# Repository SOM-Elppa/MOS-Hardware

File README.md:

# MOS-Hardware
Modules for the MOS

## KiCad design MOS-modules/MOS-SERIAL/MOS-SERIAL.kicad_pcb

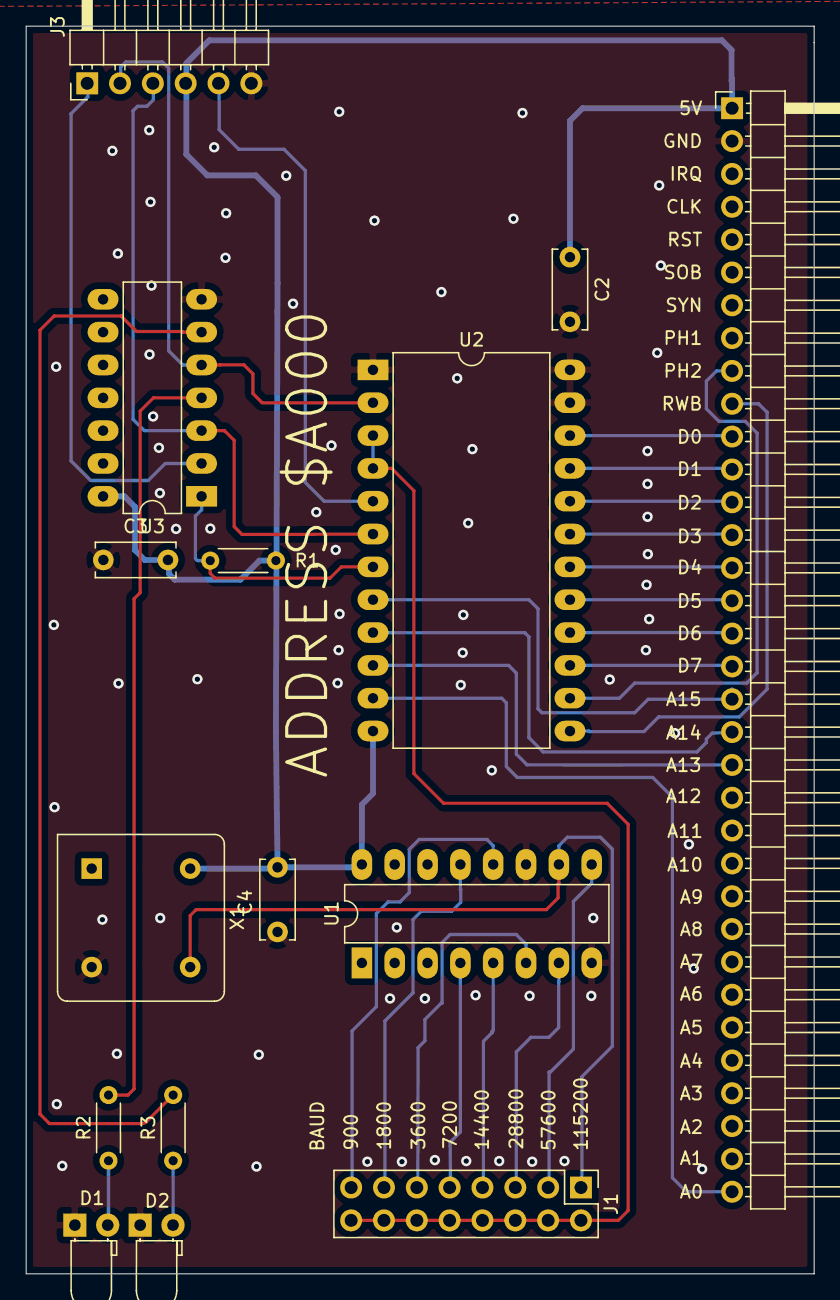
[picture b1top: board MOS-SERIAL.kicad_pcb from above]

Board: 2 copper layers, 61.0 x 96.5 mm, 15 parts (0 on the bottom side), 34 nets.

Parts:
C2: 100µF; C_Disc_D6.0mm_W2.5mm_P5.00mm
C3, C4: 100nF; C_Disc_D6.0mm_W2.5mm_P5.00mm
D1: LED TX; LED_D3.0mm_Horizontal_O1.27mm_Z2.0mm
D2: LED RX; LED_D3.0mm_Horizontal_O1.27mm_Z2.0mm
J1: Conn_02x08_Odd_Even; PinHeader_2x08_P2.54mm_Vertical
J2: Conn_01x34_Male; PinHeader_1x34_P2.54mm_Horizontal
J3: FTDI; PinHeader_1x06_P2.54mm_Horizontal
R1: 2k2; R_Axial_DIN0204_L3.6mm_D1.6mm_P5.08mm_Horizontal
R2, R3: 330R; R_Axial_DIN0204_L3.6mm_D1.6mm_P5.08mm_Horizontal
U1: 4020; DIP-16_W7.62mm_LongPads
U2: MC68B50; DIP-24_W15.24mm_LongPads
U3: 74LS04; DIP-14_W7.62mm_LongPads
X1: CXO_DIP8; Oscillator_DIP-8

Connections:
+5V: C2.1, C3.1, C4.1, J2.1, J3.4, R1.2, U1.16, U2.12, U3.14, X1.8
/900: J1.15, U1.12
/1800: J1.13, U1.13
/3600: J1.11, U1.6
/7200: J1.9, U1.4
/14400: J1.7, U1.5
/28800: J1.5, U1.7
/57600: J1.3, U1.9
/115200: J1.1, U1.10, X1.5
/A0: J2.34, U2.11
/A13: J2.21, U2.10
/A14: J2.20, U2.9
/A15: J2.19, U2.8
/CLK_SERIAL: J1.2, J1.4, J1.6, J1.8, J1.10, J1.12, J1.14, J1.16, U2.3, U2.4
/CTS: J3.5, U2.5
/D0: J2.11, U2.22
/D1: J2.12, U2.21
/D2: J2.13, U2.20
/D3: J2.14, U2.19
/D4: J2.15, U2.18
/D5: J2.16, U2.17
/D6: J2.17, U2.16
/D7: J2.18, U2.15
/DTR: J3.1, U3.2
/PHI2: J2.9, U2.14
/RWB: J2.10, U2.13
/RX: J3.2, U2.2, U3.5
/RXLED: D2.2, R3.1
/TX: J3.3, U2.6, U3.3
/TXLED: D1.2, R2.1
GND: C2.2, C3.2, C4.2, D1.1, D2.1, J2.2, J3.6, U1.8, U1.11, U2.1, U2.23, U2.24, U3.7, X1.4
unnamed: R1.1, U2.7, U3.1
unnamed: R2.2, U3.4
unnamed: R3.2, U3.6

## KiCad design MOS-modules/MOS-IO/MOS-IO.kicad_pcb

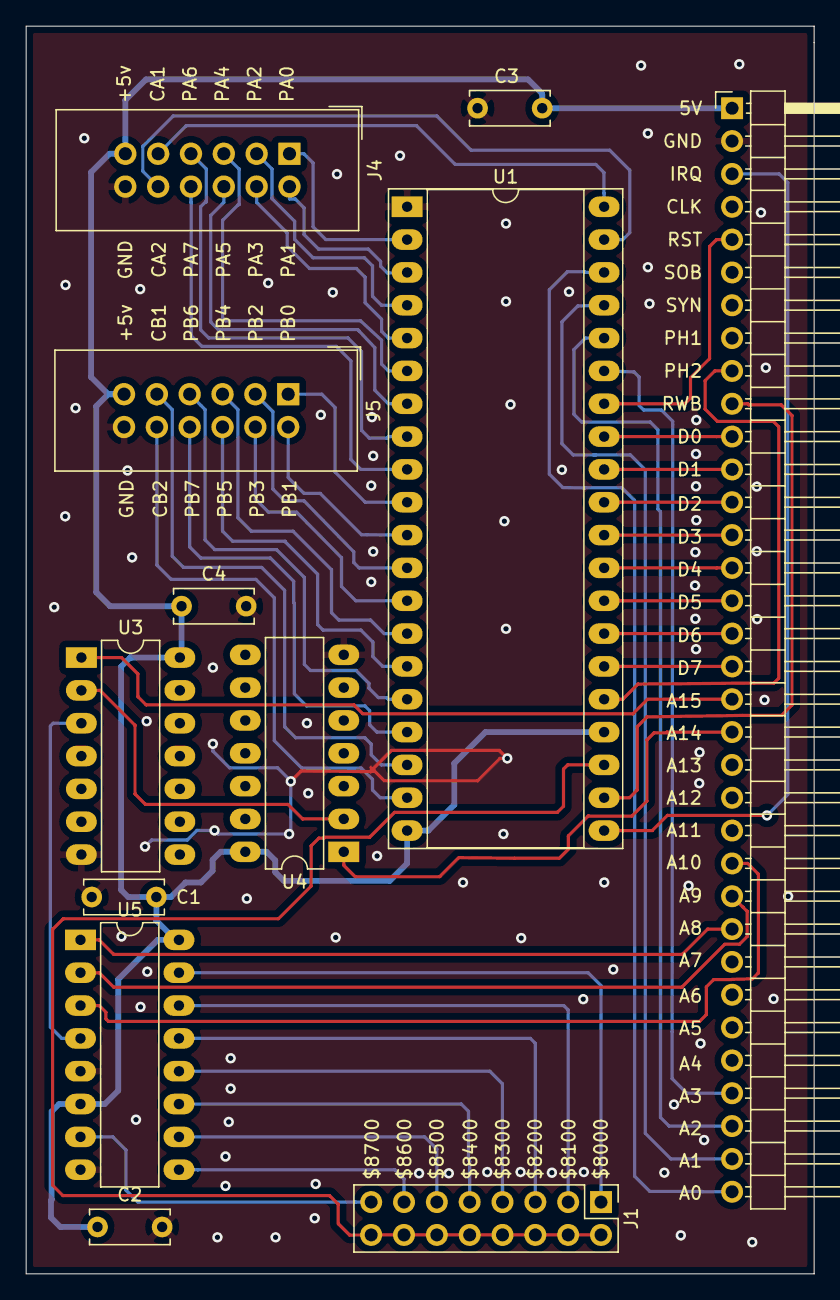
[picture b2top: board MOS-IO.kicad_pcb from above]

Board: 2 copper layers, 61.0 x 96.5 mm, 12 parts (0 on the bottom side), 54 nets.

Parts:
C1, C2, C3, C4: 100nF; C_Disc_D6.0mm_W2.5mm_P5.00mm
J1: SEL. DIRECC; PinHeader_2x08_P2.54mm_Vertical
J2: BUS CONN.; PinHeader_1x34_P2.54mm_Horizontal
J4, J5: Conn_02x06_Top_Bottom; IDC-Header_2x06_P2.54mm_Vertical
U1: 6522; DIP-40_W15.24mm_Socket_LongPads
U3: 74LS00; DIP-14_W7.62mm_LongPads
U4: 74LS04; DIP-14_W7.62mm_LongPads
U5: 74LS138; DIP-16_W7.62mm_LongPads

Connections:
+5V: C1.1, C2.1, C3.1, C4.1, J2.1, J4.11, J5.11, U1.20, U1.24, U3.14, U4.14, U5.6, U5.16
/$8000: J1.1, U5.15
/$8100: J1.3, U5.14
/$8200: J1.5, U5.13
/$8300: J1.7, U5.12
/$8400: J1.9, U5.11
/$8500: J1.11, U5.10
/$8600: J1.13, U5.9
/$8700: J1.15, U5.7
/A0: J2.34, U1.38
/A1: J2.33, U1.37
/A2: J2.32, U1.36
/A3: J2.31, U1.35
/A8: J2.26, U5.1
/A9: J2.25, U5.2
/A10: J2.24, U5.3
/A14: J2.20, U4.1
/A15: J2.19, U3.1
/CA1: J4.9, U1.40
/CA2: J4.10, U1.39
/CB1: J5.9, U1.18
/CB2: J5.10, U1.19
/CS2: J1.2, J1.4, J1.6, J1.8, J1.10, J1.12, J1.14, J1.16, U1.23
/D0: J2.11, U1.33
/D1: J2.12, U1.32
/D2: J2.13, U1.31
/D3: J2.14, U1.30
/D4: J2.15, U1.29
/D5: J2.16, U1.28
/D6: J2.17, U1.27
/D7: J2.18, U1.26
/IRQ: J2.3, U1.21
/PA0: J4.1, U1.2
/PA1: J4.2, U1.3
/PA2: J4.3, U1.4
/PA3: J4.4, U1.5
/PA4: J4.5, U1.6
/PA5: J4.6, U1.7
/PA6: J4.7, U1.8
/PA7: J4.8, U1.9
/PB0: J5.1, U1.10
/PB1: J5.2, U1.11
/PB2: J5.3, U1.12
/PB3: J5.4, U1.13
/PB4: J5.5, U1.14
/PB5: J5.6, U1.15
/PB6: J5.7, U1.16
/PB7: J5.8, U1.17
/PHI2: J2.9, U1.25
/RESET: J2.5, U1.34
/RWB: J2.10, U1.22
GND: C1.2, C2.2, C3.2, C4.2, J2.2, J4.12, J5.12, U1.1, U3.7, U4.7, U5.5, U5.8
unnamed: U3.2, U4.2
unnamed: U3.3, U5.4

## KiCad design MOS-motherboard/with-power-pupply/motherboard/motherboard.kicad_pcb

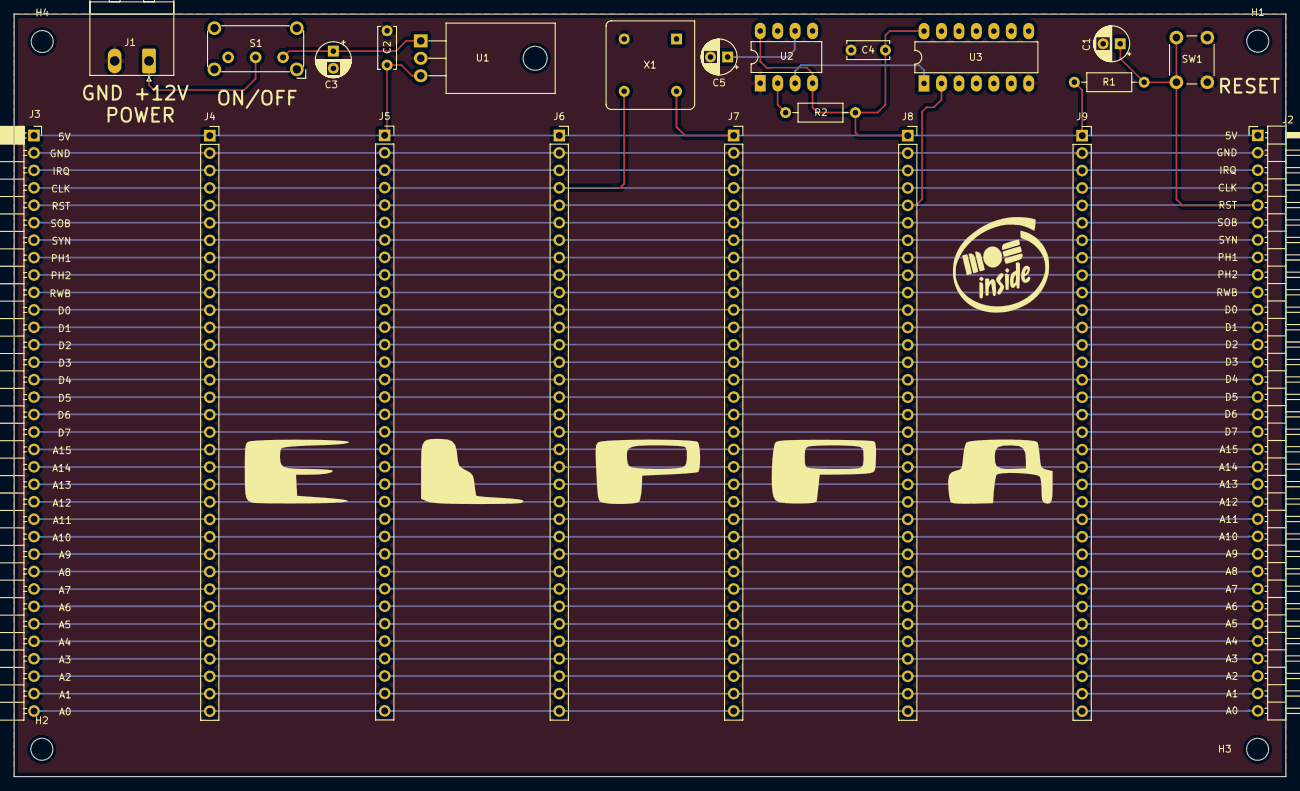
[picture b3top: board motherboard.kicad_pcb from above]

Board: 2 copper layers, 185.2 x 111.0 mm, 26 parts (0 on the bottom side), 39 nets.

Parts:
C1, C5: 0.1µF; CP_Radial_D5.0mm_P2.50mm
C2: 100µF; C_Disc_D6.0mm_W2.5mm_P5.00mm
C3: CP; CP_Radial_D5.0mm_P2.50mm
C4: 0.1µF; C_Disc_D6.0mm_W2.5mm_P5.00mm
H1, H2, H3, H4: MountingHole; MountingHole_3.2mm_M3
J1: Screw_Terminal_01x02; PhoenixContact_MSTBA_2,5_2-G_1x02_P5.00mm_Horizontal
J2: Conn_01x34_Male; PinHeader_1x34_P2.54mm_Horizontal
J3: Conn_01x34_Female; PinSocket_1x34_P2.54mm_Horizontal
J4, J5, J6, J7, J8, J9: Conn_01x34_Female; PinSocket_1x34_P2.54mm_Vertical
R1: 1KΩ; R_Axial_DIN0207_L6.3mm_D2.5mm_P10.16mm_Horizontal
R2: 1MΩ; R_Axial_DIN0207_L6.3mm_D2.5mm_P10.16mm_Horizontal
S1: EG1218; SW_E-Switch_EG1224_SPDT_Angled
SW1: SW_Push; SW_PUSH_6mm_H4.3mm
U1: L7805CV; TO-220-3_Horizontal_TabDown
U2: LM555CN_NOPB; DIP-8_W7.62mm_LongPads
U3: 74LS05; DIP-14_W7.62mm_LongPads
X1: CXO_DIP8; Oscillator_DIP-8

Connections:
+5V: C2.1, C4.1, J2.1, J3.1, J4.1, J5.1, J6.1, J7.1, J8.1, J9.1, R1.2, R2.2, U1.3, U2.4, U2.8, U3.14, X1.8
/A0: J2.34, J3.34, J4.34, J5.34, J6.34, J7.34, J8.34, J9.34
/A1: J2.33, J3.33, J4.33, J5.33, J6.33, J7.33, J8.33, J9.33
/A2: J2.32, J3.32, J4.32, J5.32, J6.32, J7.32, J8.32, J9.32
/A3: J2.31, J3.31, J4.31, J5.31, J6.31, J7.31, J8.31, J9.31
/A4: J2.30, J3.30, J4.30, J5.30, J6.30, J7.30, J8.30, J9.30
/A5: J2.29, J3.29, J4.29, J5.29, J6.29, J7.29, J8.29, J9.29
/A6: J2.28, J3.28, J4.28, J5.28, J6.28, J7.28, J8.28, J9.28
/A7: J2.27, J3.27, J4.27, J5.27, J6.27, J7.27, J8.27, J9.27
/A8: J2.26, J3.26, J4.26, J5.26, J6.26, J7.26, J8.26, J9.26
/A9: J2.25, J3.25, J4.25, J5.25, J6.25, J7.25, J8.25, J9.25
/A10: J2.24, J3.24, J4.24, J5.24, J6.24, J7.24, J8.24, J9.24
/A11: J2.23, J3.23, J4.23, J5.23, J6.23, J7.23, J8.23, J9.23
/A12: J2.22, J3.22, J4.22, J5.22, J6.22, J7.22, J8.22, J9.22
/A13: J2.21, J3.21, J4.21, J5.21, J6.21, J7.21, J8.21, J9.21
/A14: J2.20, J3.20, J4.20, J5.20, J6.20, J7.20, J8.20, J9.20
/A15: J2.19, J3.19, J4.19, J5.19, J6.19, J7.19, J8.19, J9.19
/CLK: J2.4, J3.4, J4.4, J5.4, J6.4, J7.4, J8.4, J9.4, X1.5
/D0: J2.11, J3.11, J4.11, J5.11, J6.11, J7.11, J8.11, J9.11
/D1: J2.12, J3.12, J4.12, J5.12, J6.12, J7.12, J8.12, J9.12
/D2: J2.13, J3.13, J4.13, J5.13, J6.13, J7.13, J8.13, J9.13
/D3: J2.14, J3.14, J4.14, J5.14, J6.14, J7.14, J8.14, J9.14
/D4: J2.15, J3.15, J4.15, J5.15, J6.15, J7.15, J8.15, J9.15
/D5: J2.16, J3.16, J4.16, J5.16, J6.16, J7.16, J8.16, J9.16
/D6: J2.17, J3.17, J4.17, J5.17, J6.17, J7.17, J8.17, J9.17
/D7: J2.18, J3.18, J4.18, J5.18, J6.18, J7.18, J8.18, J9.18
/IRQ: J2.3, J3.3, J4.3, J5.3, J6.3, J7.3, J8.3, J9.3
/PHI1: J2.8, J3.8, J4.8, J5.8, J6.8, J7.8, J8.8, J9.8
/PHI2: J2.9, J3.9, J4.9, J5.9, J6.9, J7.9, J8.9, J9.9
/RESET: C1.1, J2.5, J3.5, J4.5, J5.5, J6.5, J7.5, J8.5, J9.5, R1.1, SW1.2, U3.2
/RWB: J2.10, J3.10, J4.10, J5.10, J6.10, J7.10, J8.10, J9.10
/SOB: J2.6, J3.6, J4.6, J5.6, J6.6, J7.6, J8.6, J9.6
/SYNC: J2.7, J3.7, J4.7, J5.7, J6.7, J7.7, J8.7, J9.7
GND: C1.2, C2.2, C3.2, C4.2, C5.2, J1.2, J2.2, J3.2, J4.2, J5.2, J6.2, J7.2, J8.2, J9.2, SW1.1, U1.2, U2.1, U3.7, X1.4
unnamed: C3.1, S1.1, U1.1
unnamed: C5.1, U2.6
unnamed: J1.1, S1.2
unnamed: R2.1, U2.2
unnamed: U2.3, U3.1

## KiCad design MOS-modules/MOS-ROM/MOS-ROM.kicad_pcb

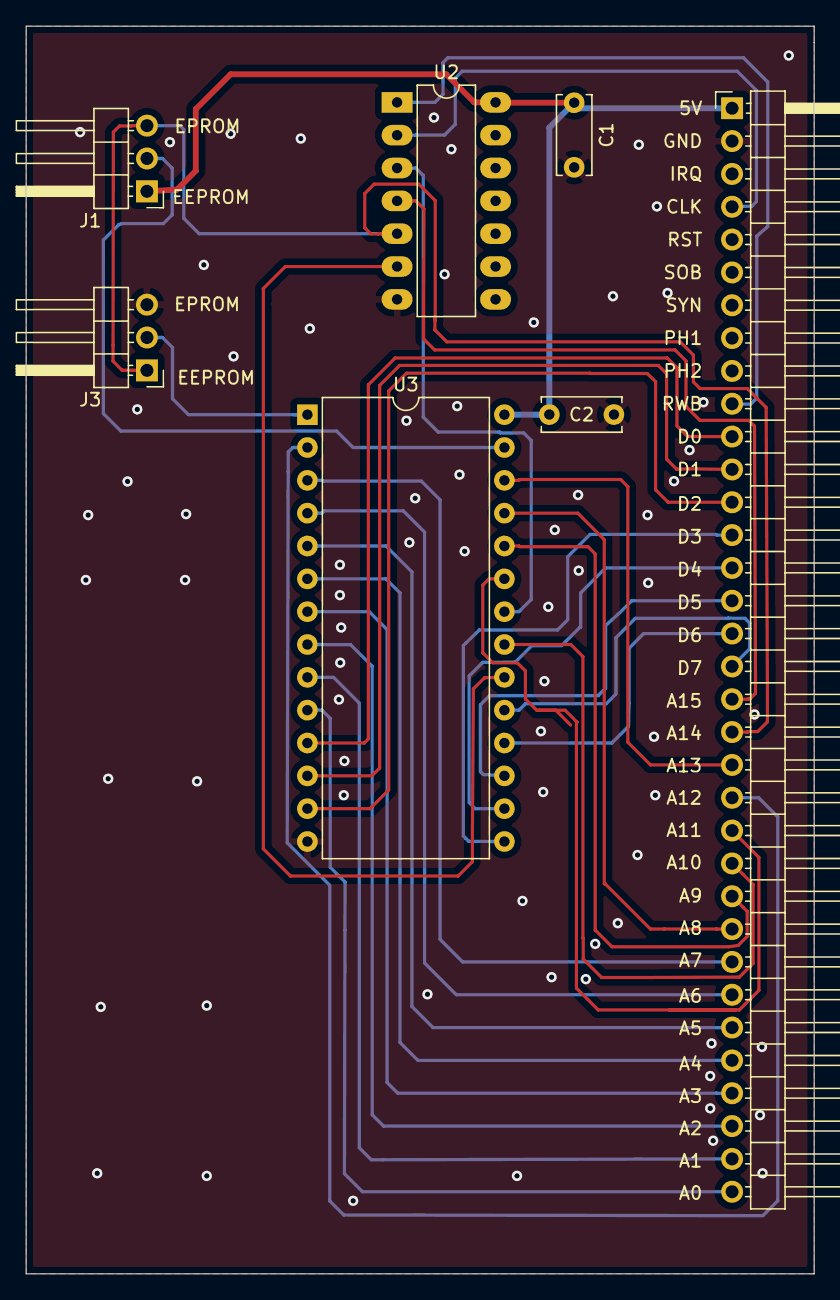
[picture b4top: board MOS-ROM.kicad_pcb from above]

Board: 2 copper layers, 61.0 x 96.5 mm, 7 parts (0 on the bottom side), 32 nets.

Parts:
C1, C2: 100µF; C_Disc_D6.0mm_W2.5mm_P5.00mm
J1, J3: Conn_01x03_Male; PinHeader_1x03_P2.54mm_Horizontal
J2: Conn_01x34_Male; PinHeader_1x34_P2.54mm_Horizontal
U2: 74LS00; DIP-14_W7.62mm_LongPads
U3: 27C512; DIP-28_W15.24mm

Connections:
+5V: C1.1, C2.1, J1.1, J2.1, U2.14, U3.28
/A0: J2.34, U3.10
/A1: J2.33, U3.9
/A2: J2.32, U3.8
/A3: J2.31, U3.7
/A4: J2.30, U3.6
/A5: J2.29, U3.5
/A6: J2.28, U3.4
/A7: J2.27, U3.3
/A8: J2.26, U3.25
/A9: J2.25, U3.24
/A10: J2.24, U3.21
/A11: J2.23, U3.23
/A12: J2.22, U3.2
/A13: J2.21, U3.26
/A14: J1.3, J2.20, J3.1, U2.5
/A15: J2.19, U2.4
/CE-CS: U2.6, U3.20
/CLK: J2.4, U2.2
/D0: J2.11, U3.11
/D1: J2.12, U3.12
/D2: J2.13, U3.13
/D3: J2.14, U3.15
/D4: J2.15, U3.16
/D5: J2.16, U3.17
/D6: J2.17, U3.18
/D7: J2.18, U3.19
/OE: U2.3, U3.22
/PIN1: J3.2, U3.1
/PIN27: J1.2, U3.27
/RWB: J2.10, U2.1
GND: C1.2, C2.2, J2.2, J3.3, U2.7, U3.14

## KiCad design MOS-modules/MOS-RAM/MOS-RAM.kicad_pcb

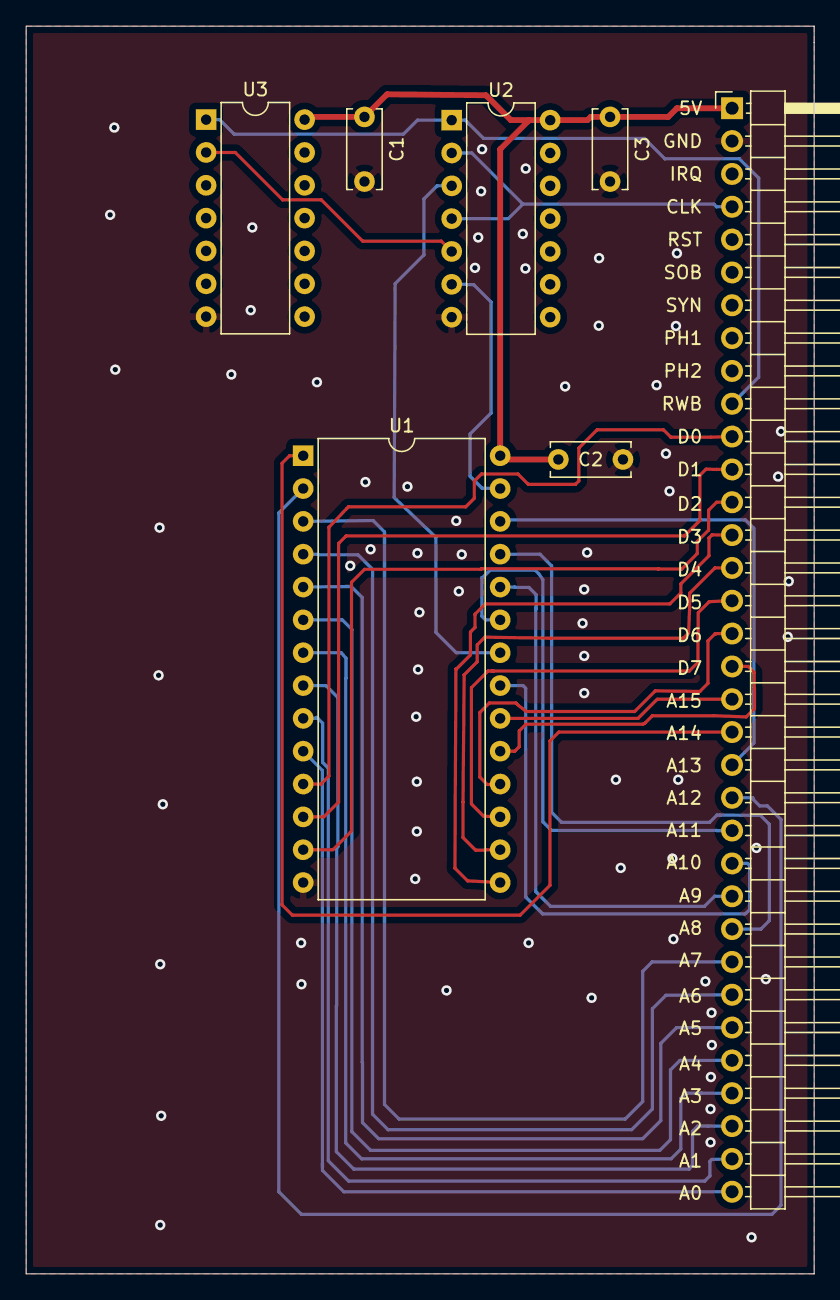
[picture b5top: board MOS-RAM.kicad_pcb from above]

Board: 2 copper layers, 61.0 x 96.5 mm, 7 parts (0 on the bottom side), 31 nets.

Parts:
C1, C2, C3: 100µF; C_Disc_D6.0mm_W2.5mm_P5.00mm
J2: Conn_01x34_Male; PinHeader_1x34_P2.54mm_Horizontal
U1: HM62256BLP; DIP-28_W15.24mm
U2: 74LS00; DIP-14_W7.62mm
U3: 74LS04; DIP-14_W7.62mm

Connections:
+5V: C1.1, C2.1, C3.1, J2.1, U1.28, U2.14, U3.14
/A0: J2.34, U1.10
/A1: J2.33, U1.9
/A2: J2.32, U1.8
/A3: J2.31, U1.7
/A4: J2.30, U1.6
/A5: J2.29, U1.5
/A6: J2.28, U1.4
/A7: J2.27, U1.3
/A8: J2.26, U1.25
/A9: J2.25, U1.24
/A10: J2.24, U1.21
/A11: J2.23, U1.23
/A12: J2.22, U1.2
/A13: J2.21, U1.26
/A14: J2.20, U1.1
/A15: J2.19, U1.20
/CLK: J2.4, U2.2, U2.4
/D0: J2.11, U1.11
/D1: J2.12, U1.12
/D2: J2.13, U1.13
/D3: J2.14, U1.15
/D4: J2.15, U1.16
/D5: J2.16, U1.17
/D6: J2.17, U1.18
/D7: J2.18, U1.19
/RWB: J2.10, U2.1, U3.1
GND: C1.2, C2.2, C3.2, J2.2, U1.14, U2.7, U3.7
unnamed: U1.22, U2.3
unnamed: U1.27, U2.6
unnamed: U2.5, U3.2

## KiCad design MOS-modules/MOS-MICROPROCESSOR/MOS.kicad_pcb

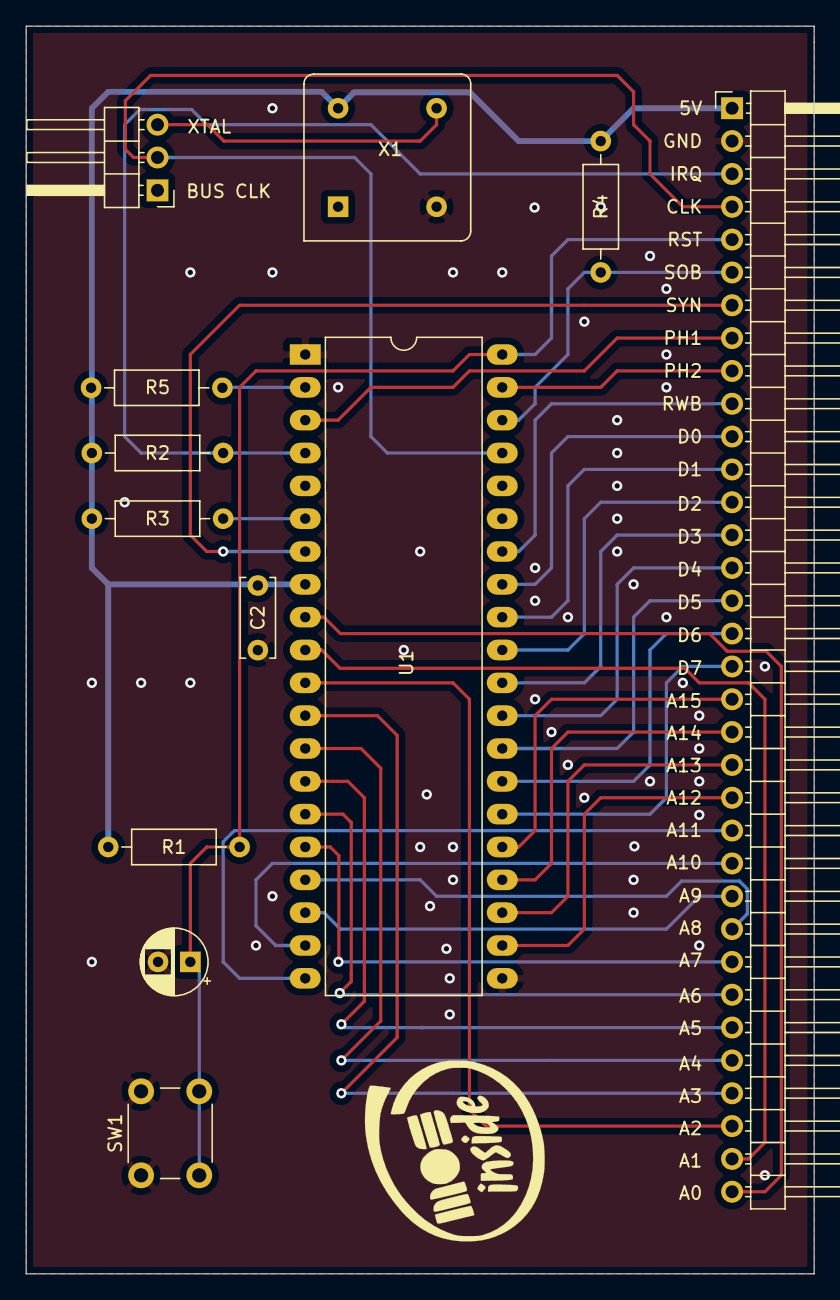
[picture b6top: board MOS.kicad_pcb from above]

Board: 2 copper layers, 61.0 x 96.5 mm, 12 parts (0 on the bottom side), 37 nets.

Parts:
C1: 0.1µF; CP_Radial_D5.0mm_P2.50mm
C2: 100µF; C_Disc_D6.0mm_W2.5mm_P5.00mm
J1: Conn_01x03_Male; PinHeader_1x03_P2.54mm_Horizontal
J2: Conn_01x34_Male; PinHeader_1x34_P2.54mm_Horizontal
R1, R2, R3, R4, R5: 1KΩ; R_Axial_DIN0207_L6.3mm_D2.5mm_P10.16mm_Horizontal
SW1: SW_Push; SW_PUSH_6mm_H7.3mm
U1: 6502; DIP-40_W15.24mm_LongPads
X1: CXO_DIP8; Oscillator_DIP-8

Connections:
+5V: C2.1, J2.1, R1.2, R2.2, R3.2, R4.2, R5.2, U1.8, X1.8
/A0: J2.34, U1.9
/A1: J2.33, U1.10
/A2: J2.32, U1.11
/A3: J2.31, U1.12
/A4: J2.30, U1.13
/A5: J2.29, U1.14
/A6: J2.28, U1.15
/A7: J2.27, U1.16
/A8: J2.26, U1.17
/A9: J2.25, U1.18
/A10: J2.24, U1.19
/A11: J2.23, U1.20
/A12: J2.22, U1.22
/A13: J2.21, U1.23
/A14: J2.20, U1.24
/A15: J2.19, U1.25
/CLK: J1.2, J2.4, U1.37
/CLK_INTERNAL: J1.3, X1.5
/D0: J2.11, U1.33
/D1: J2.12, U1.32
/D2: J2.13, U1.31
/D3: J2.14, U1.30
/D4: J2.15, U1.29
/D5: J2.16, U1.28
/D6: J2.17, U1.27
/D7: J2.18, U1.26
/IRQ: J2.3, R2.1, U1.4
/PHI1: J2.8, U1.3
/PHI2: J2.9, U1.39
/RESET: C1.1, J2.5, R1.1, SW1.2, U1.40
/RWB: J2.10, U1.34
/SOB: J2.6, R4.1, U1.38
/SYNC: J2.7, U1.7
GND: C1.2, C2.2, J2.2, SW1.1, U1.1, U1.21, X1.4
unnamed: R3.1, U1.6
unnamed: R5.1, U1.2

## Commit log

2020-11-06 added .gitignore file
2020-11-06 MOS 6502 module added
2020-11-06 MOS 6503 Rev B
2020-11-06 added RAM module
2020-11-06 added ROM module
2020-11-06 added motherboard with power supply
2020-11-26 fixed typo in folder
2020-11-26 Module IO rev A added
2020-11-26 Module serial rev A added
